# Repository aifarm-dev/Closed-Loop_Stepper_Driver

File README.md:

# AI_FARM Closed-Loop_Stepper_Driver Board

## Descriptions 

### Image Referefence

## Schematics 

## 3D Design  

### PCB FRONT

### PCB BACK

## PCB Design

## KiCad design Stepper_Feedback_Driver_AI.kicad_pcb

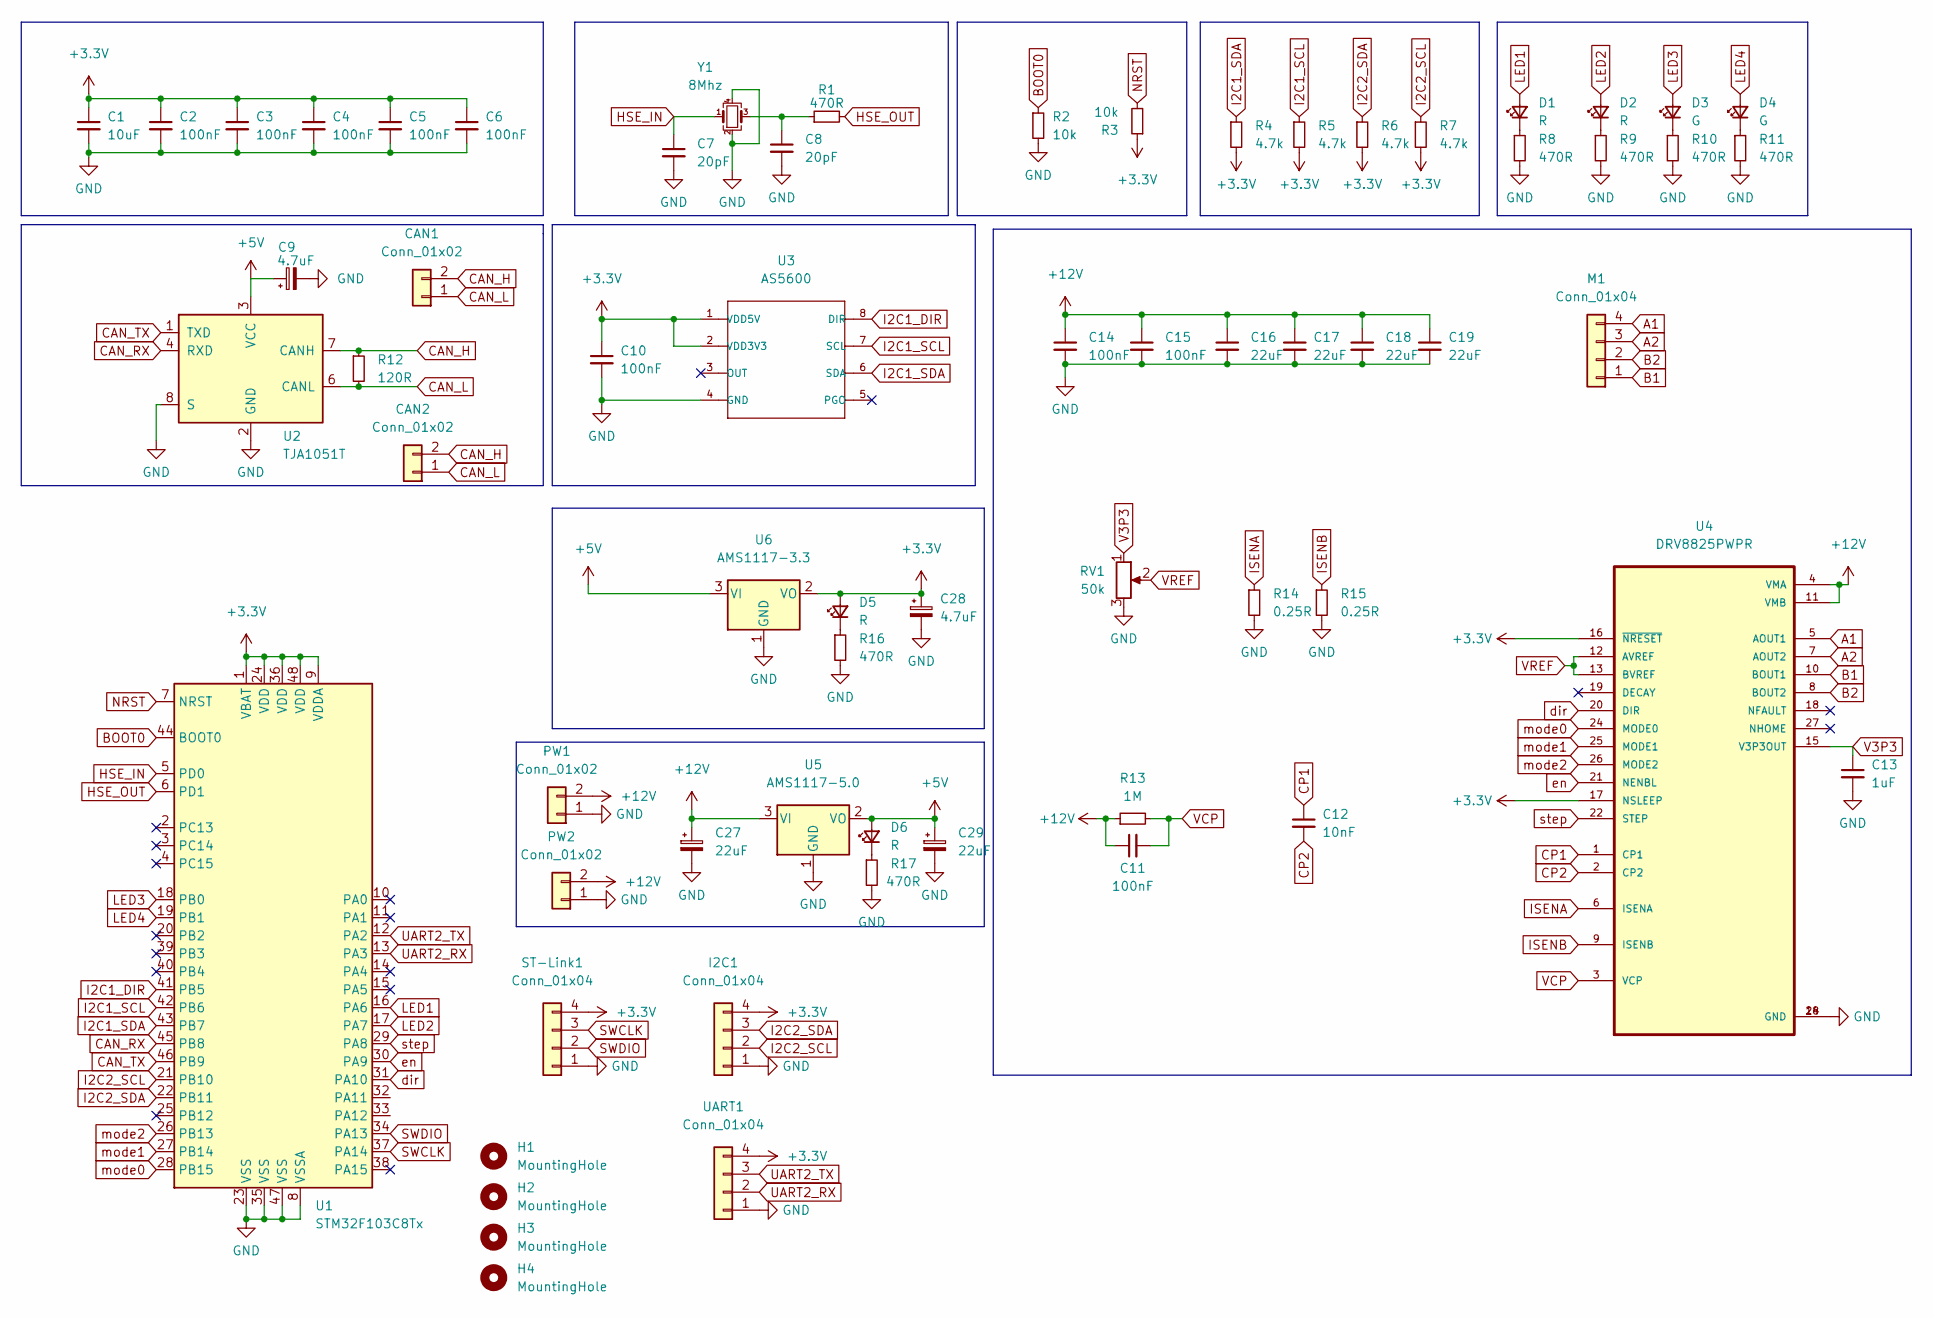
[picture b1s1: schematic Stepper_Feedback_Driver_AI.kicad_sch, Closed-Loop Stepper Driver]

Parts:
C1: 10uF; C_0805_2012Metric
C2, C3, C4, C5, C6, C10, C11, C14, C15: 100nF; C_0603_1608Metric
C7, C8: 20pF; C_0603_1608Metric
C9, C28: 4.7uF; CP_EIA-3216-10_Kemet-I
C12: 10nF; C_0603_1608Metric
C13: 1uF; C_0603_1608Metric
C16, C17, C18, C19: 22uF; C_1206_3216Metric
C27, C29: 22uF; CP_EIA-3216-10_Kemet-I
CAN1, CAN2: Conn_01x02; ConPadx02_small
D1, D2, D5, D6: R; LED_0603_1608Metric
D3, D4: G; LED_0603_1608Metric
H1, H2, H3, H4: MountingHole; MountingHole_3mm_Pad
I2C1: Conn_01x04; ConPadx04
M1: Conn_01x04; ConPadx04
PW1, PW2: Conn_01x02; ConPadx02
R1, R8, R9, R10, R11, R16, R17: 470R; R_0603_1608Metric
R2, R3: 10k; R_0603_1608Metric
R4, R5, R6, R7: 4.7k; R_0603_1608Metric
R12: 120R; R_0603_1608Metric
R13: 1M; R_0603_1608Metric
R14, R15: 0.25R; R_0805_2012Metric
RV1: 50k; Potentiometer_Bourns_TC33X_Vertical
ST-Link1: Conn_01x04; ConPadx04
U1: STM32F103C8Tx; LQFP-48_7x7mm_P0.5mm
U2: TJA1051T; SOIC-8_3.9x4.9mm_P1.27mm
U3: AS5600; SOIC-8_3.9x4.9mm_P1.27mm
U4: DRV8825PWPR; IC_TPS61196PWPRQ1
U5: AMS1117-5.0; SOT-223-3_TabPin2
U6: AMS1117-3.3; SOT-223-3_TabPin2
UART1: Conn_01x04; ConPadx04
Y1: 8Mhz; Crystal_SMD_3225-4Pin_3.2x2.5mm

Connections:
+3V3: C1.1, C2.1, C3.1, C4.1, C5.1, C6.1, C10.1, C28.1, D5.2 (A), I2C1.4, R3.1, R4.2, R5.2, R6.2, R7.2, ST-Link1.4, U1.1 (VBAT), U1.9 (VDDA), U1.24 (VDD), U1.36 (VDD), U1.48 (VDD), U3.1 (VDD5V), U3.2 (VDD3V3), U4.16 (~NRESET), U4.17 (NSLEEP), U6.2 (VO), UART1.4
+5V: C9.1, C29.1, D6.2 (A), U2.3 (VCC), U5.2 (VO), U6.3 (VI)
+12V: C11.1, C14.1, C15.1, C16.1, C17.1, C18.1, C19.1, C27.1, PW1.2, PW2.2, R13.1, U4.4 (VMA), U4.11 (VMB), U5.3 (VI)
A1: M1.4, U4.5 (AOUT1)
A2: M1.3, U4.7 (AOUT2)
B1: M1.1, U4.10 (BOUT1)
B2: M1.2, U4.8 (BOUT2)
BOOT0: R2.1, U1.44 (BOOT0)
CAN_H: CAN1.2, CAN2.2, R12.1, U2.7 (CANH)
CAN_L: CAN1.1, CAN2.1, R12.2, U2.6 (CANL)
CAN_RX: U1.45 (PB8), U2.4 (RXD)
CAN_TX: U1.46 (PB9), U2.1 (TXD)
CP1: C12.1, U4.1 (CP1)
CP2: C12.2, U4.2 (CP2)
GND: C1.2, C2.2, C3.2, C4.2, C5.2, C6.2, C7.2, C8.2, C9.2, C10.2, C13.2, C14.2, C15.2, C16.2, C17.2, C18.2, C19.2, C27.2, C28.2, C29.2, I2C1.1, PW1.1, PW2.1, R2.2, R8.2, R9.2, R10.2, R11.2, R14.2, R15.2, R16.2, R17.2, RV1.3, ST-Link1.1, U1.8 (VSSA), U1.23 (VSS), U1.35 (VSS), U1.47 (VSS), U2.2 (GND), U2.8 (S), U3.4 (GND), U4.14 (GND), U4.28 (GND), U5.1 (GND), U6.1 (GND), UART1.1, Y1.2, Y1.4
HSE_IN: C7.1, U1.5 (PD0), Y1.1
HSE_OUT: R1.2, U1.6 (PD1)
I2C1_DIR: U1.41 (PB5), U3.8 (DIR)
I2C1_SCL: R5.1, U1.42 (PB6), U3.7 (SCL)
I2C1_SDA: R4.1, U1.43 (PB7), U3.6 (SDA)
I2C2_SCL: I2C1.2, R7.1, U1.21 (PB10)
I2C2_SDA: I2C1.3, R6.1, U1.22 (PB11)
ISENA: R14.1, U4.6 (ISENA)
ISENB: R15.1, U4.9 (ISENB)
LED1: D1.2 (A), U1.16 (PA6)
LED2: D2.2 (A), U1.17 (PA7)
LED3: D3.2 (A), U1.18 (PB0)
LED4: D4.2 (A), U1.19 (PB1)
NRST: R3.2, U1.7 (NRST)
unnamed: C8.1, R1.1, Y1.3
unnamed: D1.1 (K), R8.1
unnamed: D2.1 (K), R9.1
unnamed: D3.1 (K), R10.1
unnamed: D4.1 (K), R11.1
unnamed: D5.1 (K), R16.1
unnamed: D6.1 (K), R17.1
SWCLK: ST-Link1.3, U1.37 (PA14)
SWDIO: ST-Link1.2, U1.34 (PA13)
UART2_RX: U1.13 (PA3), UART1.2
UART2_TX: U1.12 (PA2), UART1.3
V3P3: C13.1, RV1.1, U4.15 (V3P3OUT)
VCP: C11.2, R13.2, U4.3 (VCP)
VREF: RV1.2, U4.12 (AVREF), U4.13 (BVREF)
dir: U1.31 (PA10), U4.20 (DIR)
en: U1.30 (PA9), U4.21 (NENBL)
mode0: U1.28 (PB15), U4.24 (MODE0)
mode1: U1.27 (PB14), U4.25 (MODE1)
mode2: U1.26 (PB13), U4.26 (MODE2)
step: U1.29 (PA8), U4.22 (STEP)

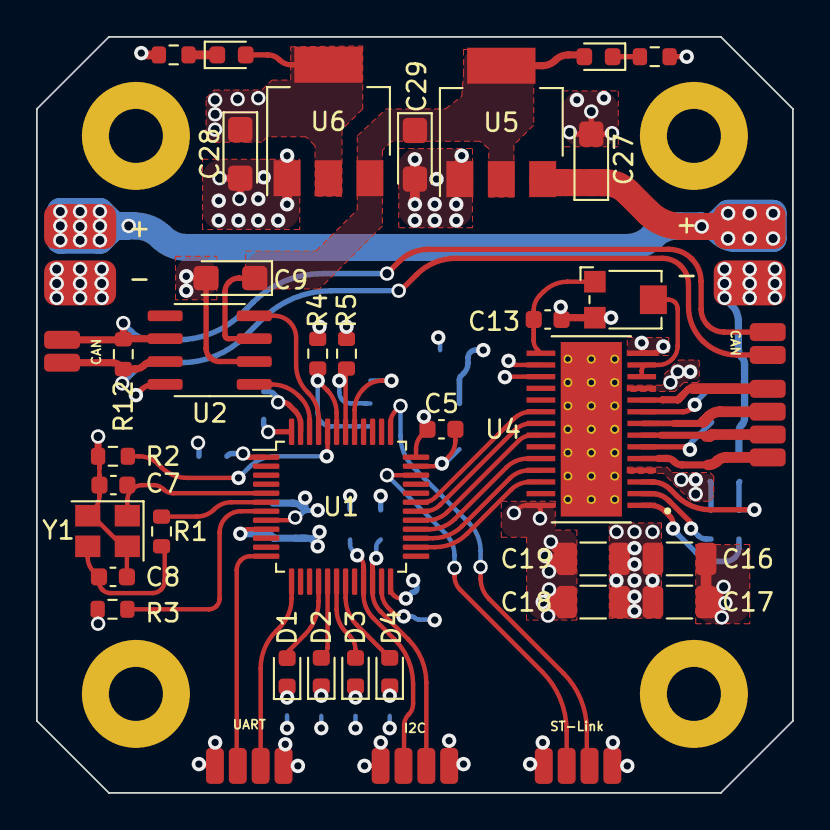
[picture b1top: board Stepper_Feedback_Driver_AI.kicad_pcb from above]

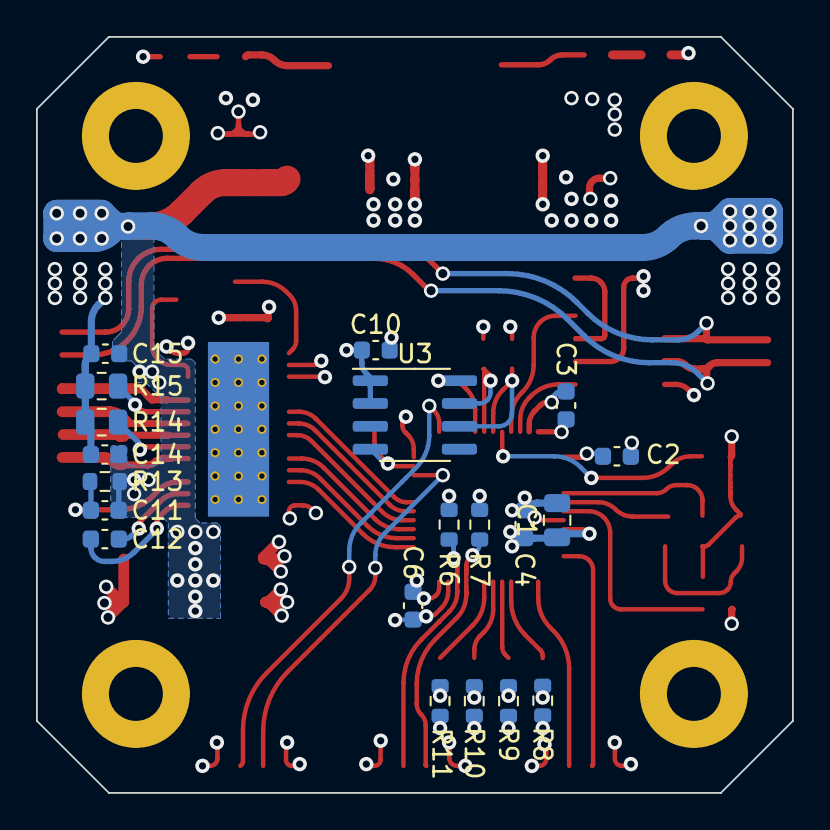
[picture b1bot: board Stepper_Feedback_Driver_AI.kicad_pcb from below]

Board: 4 copper layers, 42.0 x 42.0 mm, 65 parts (20 on the bottom side), 49 nets.

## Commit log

2022-05-11 V2.0 Initial Commit
2022-05-11 Remove Directory backup
